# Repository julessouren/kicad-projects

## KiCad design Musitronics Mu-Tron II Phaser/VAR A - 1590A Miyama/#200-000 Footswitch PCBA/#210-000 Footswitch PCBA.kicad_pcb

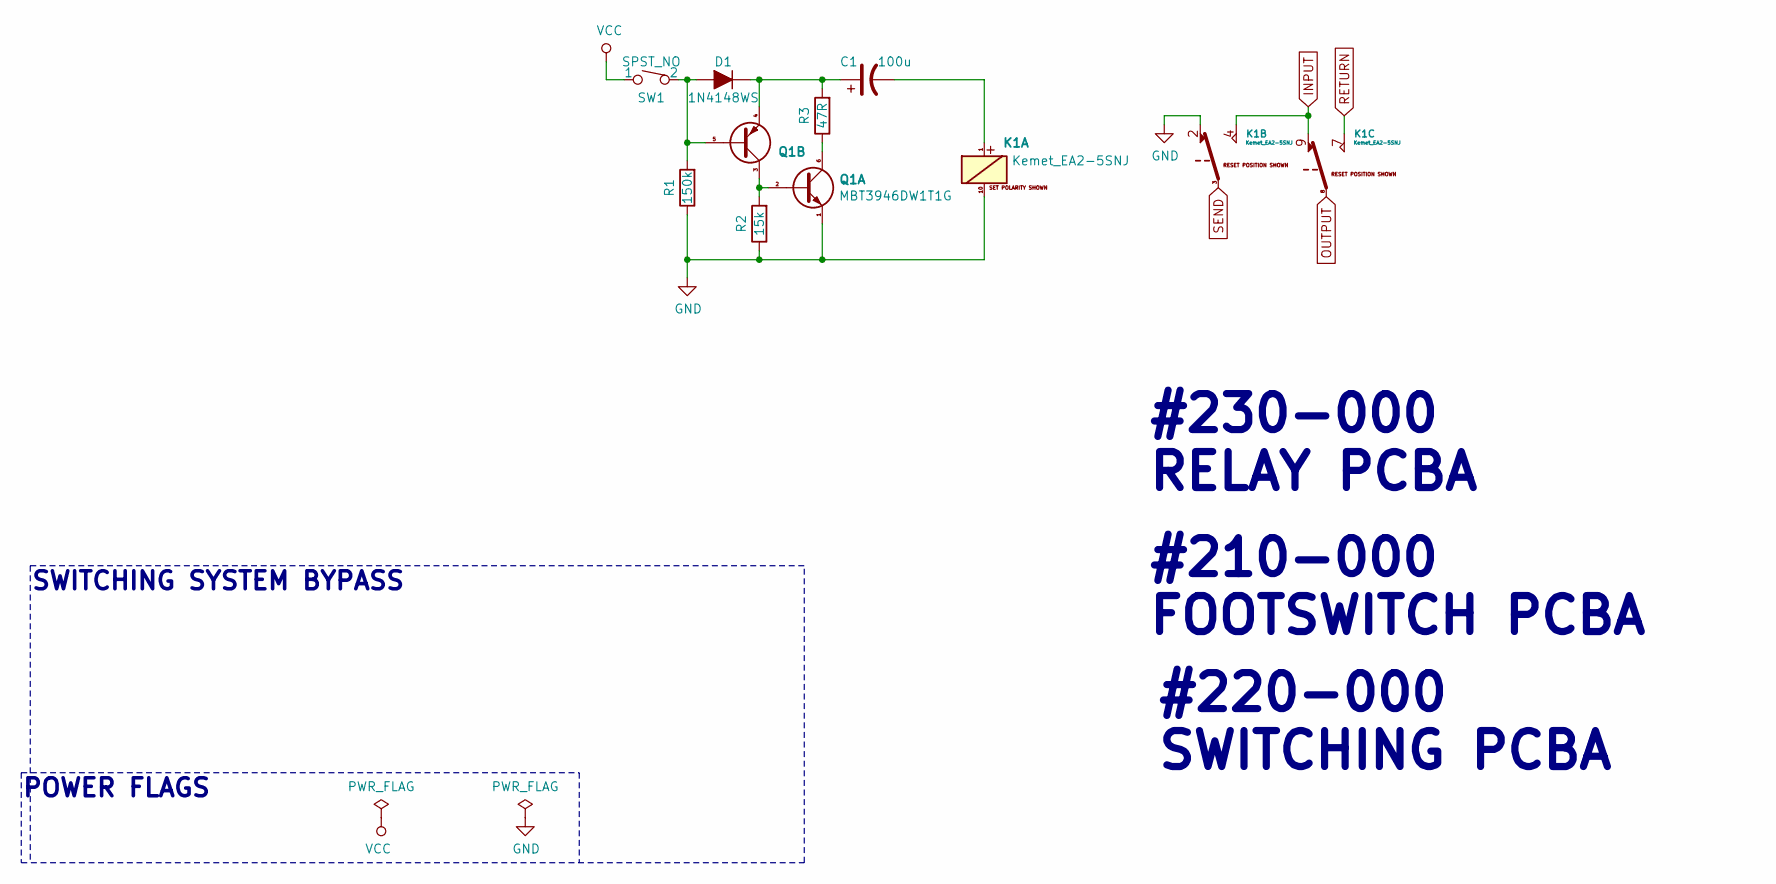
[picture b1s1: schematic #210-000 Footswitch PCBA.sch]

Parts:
C1: 100u; Nichicon_UWT1E101MCL1GS
D1: 1N4148WS; ON_Semi_1N4148WS
K1: Kemet_EA2-5SNJ; Kemet_EA2-SNJ
Q1: MBT3946DW1T1G; ON_Semi_MBT3946DW1T1G
R1: 150k; R_0603_1608M
R2: 15k; R_0603_1608M
R3: 47R; R_0603_1608M
SW1: SPST_NO; Miyama_DS-462

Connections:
GND: K1.2, K1.10, Q1.1 (E1), R1.1, R2.1
INPUT: K1.4, K1.9
unnamed: C1.1, D1.2 (K), Q1.4 (E2), R3.2
unnamed: C1.2, K1.1
unnamed: D1.1 (A), Q1.5 (B2), R1.2, SW1.2
unnamed: Q1.2 (B1), Q1.3 (C2), R2.2
unnamed: Q1.6 (C1), R3.1
OUTPUT: K1.8
RETURN: K1.7
SEND: K1.3
VCC: SW1.1

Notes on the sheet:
#210-000 FOOTSWITCH PCBA
#220-000 SWITCHING PCBA
SWITCHING SYSTEM BYPASS
POWER FLAGS
#230-000 RELAY PCBA

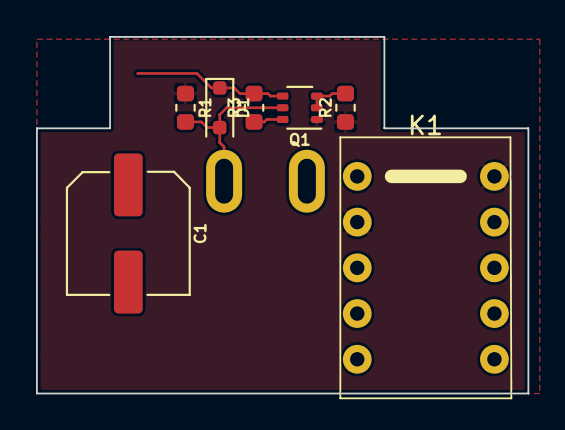
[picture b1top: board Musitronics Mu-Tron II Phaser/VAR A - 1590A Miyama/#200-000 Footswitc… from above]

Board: 2 copper layers, 27.3 x 19.8 mm, 8 parts (1 on the bottom side), 7 nets.

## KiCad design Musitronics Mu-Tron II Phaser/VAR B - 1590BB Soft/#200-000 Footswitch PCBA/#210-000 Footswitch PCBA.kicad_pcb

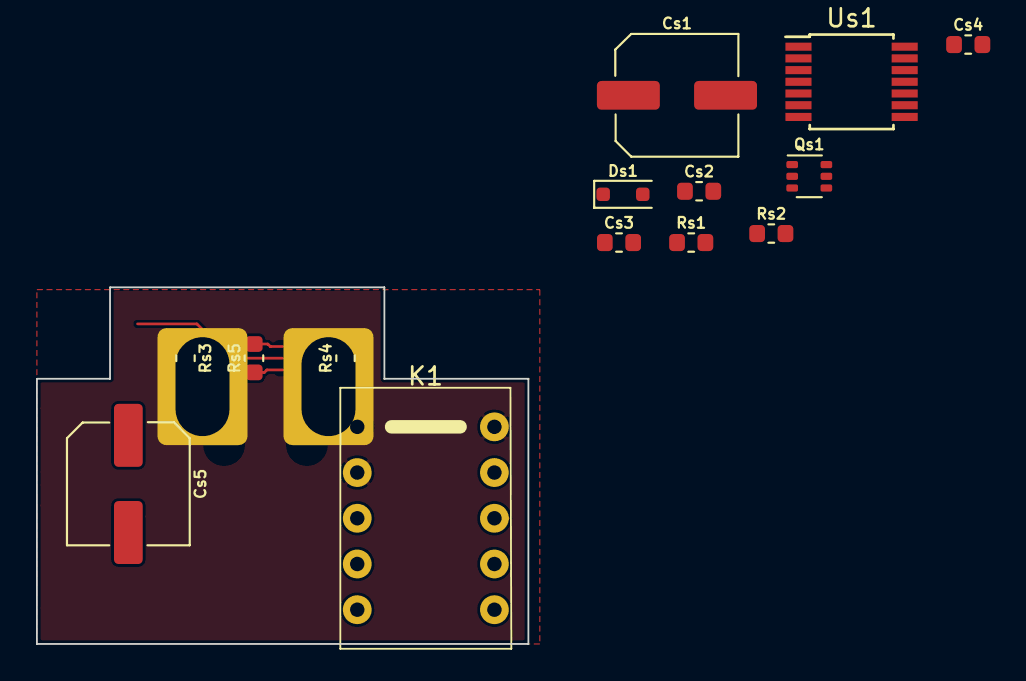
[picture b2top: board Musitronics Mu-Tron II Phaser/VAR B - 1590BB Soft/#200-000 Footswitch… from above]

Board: 2 copper layers, 27.3 x 19.8 mm, 15 parts (1 on the bottom side), 12 nets.

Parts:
Cs1, Cs5: 100u; Nichicon_UWT1E101MCL1GS
Cs2: 100n; C_0603_1608M_h0.85
Cs3: 4n7; C_0603_1608M_h0.85
Cs4: 47n; C_0603_1608M_h0.85
Ds1: 1N4148WS; ON_Semi_1N4148WS
K1: Kemet_EA2-5SNJ; Kemet_EA2-SNJ
Qs1: MBT3946DW1T1G; ON_Semi_MBT3946DW1T1G
Rs1: 100k; R_0603_1608M
Rs2: 1M; R_0603_1608M
Rs3: 150k; R_0603_1608M
Rs4: 15k; R_0603_1608M
Rs5: 47R; R_0603_1608M
SWa1: SPST_NO; R13-85A1-05-HWH
Us1: CD40106BPWR; Texas_Instruments_CD40106BPWR

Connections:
GND: Cs1.2, Cs2.2, Cs3.2, Cs4.2, K1.2, K1.10, Qs1.1, Rs3.1, Rs4.1, Us1.7, Us1.9, Us1.11, Us1.13
INPUT: K1.4, K1.9
unnamed: Cs3.1, Rs1.2, SWa1.1, Us1.1
unnamed: Cs4.1, Rs2.1, SWa1.2
unnamed: Cs5.1, Ds1.2, Qs1.4, Rs5.2
unnamed: Cs5.2, K1.1
unnamed: Ds1.1, Qs1.5, Rs3.2, Us1.6
unnamed: Qs1.2, Qs1.3, Rs4.2
unnamed: Qs1.6, Rs5.1
unnamed: Rs1.1, Us1.4, Us1.5
unnamed: Rs2.2, Us1.2, Us1.3
VCC: Cs1.1, Cs2.1, Us1.14

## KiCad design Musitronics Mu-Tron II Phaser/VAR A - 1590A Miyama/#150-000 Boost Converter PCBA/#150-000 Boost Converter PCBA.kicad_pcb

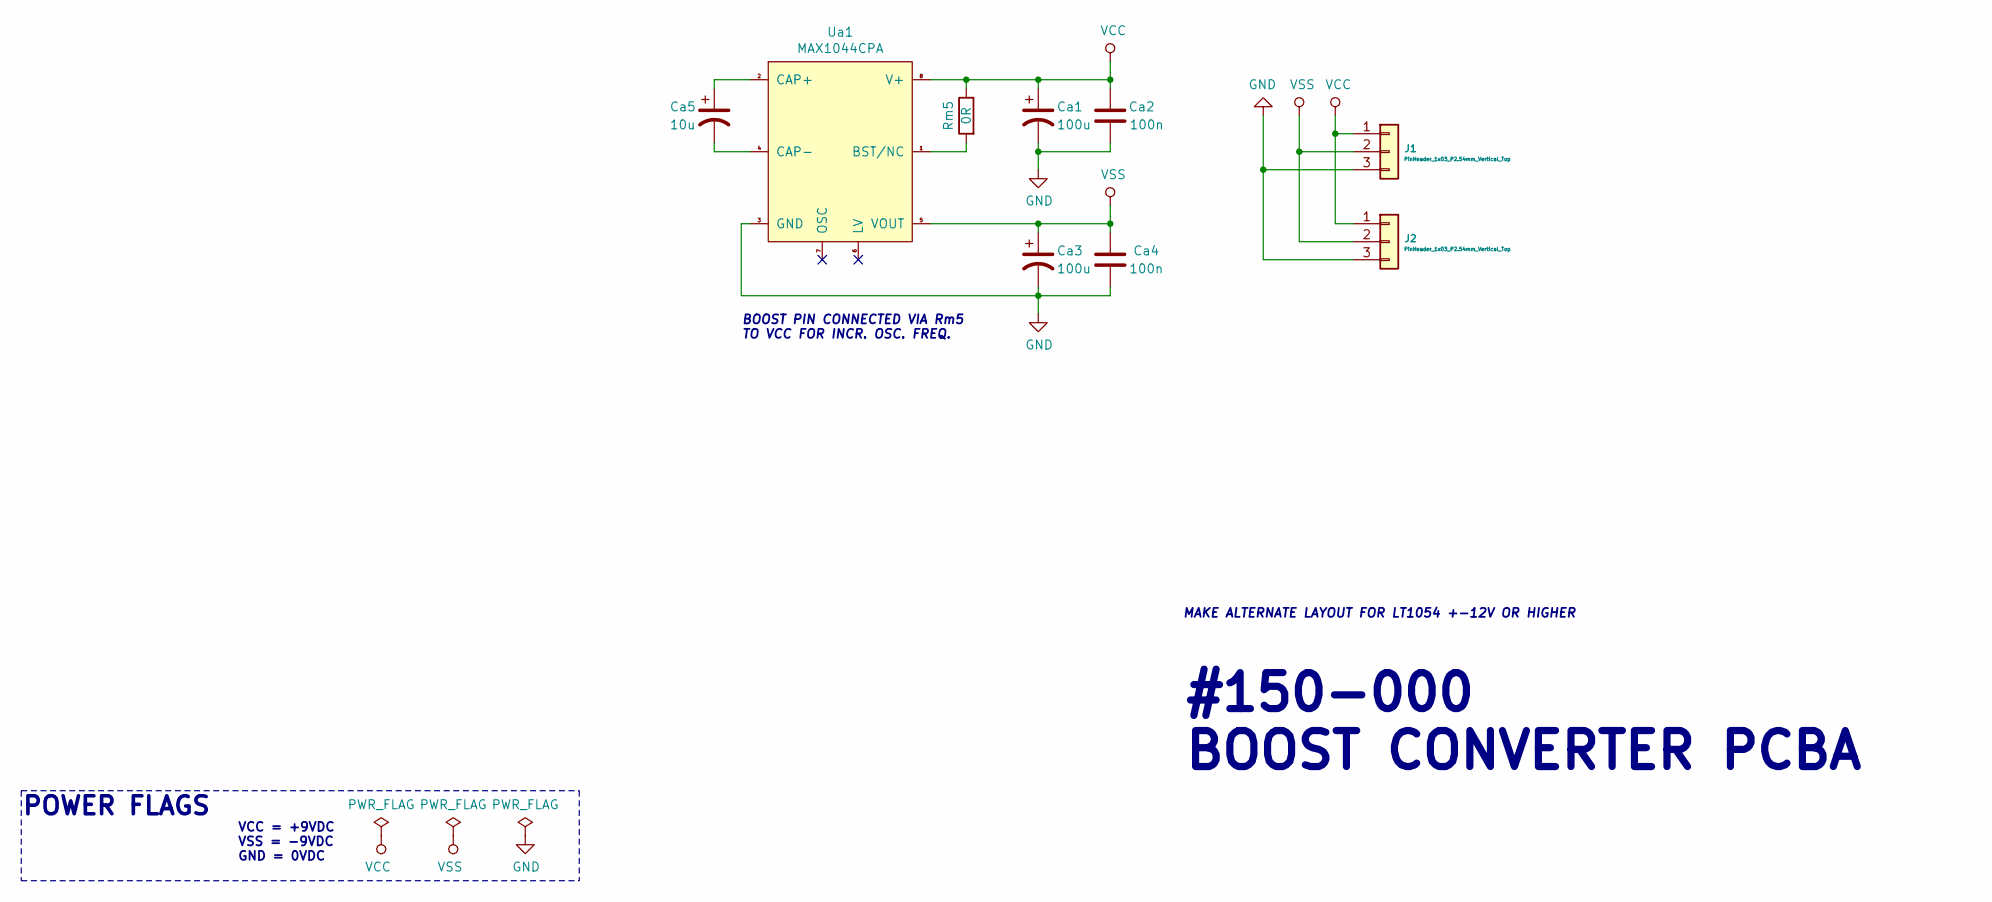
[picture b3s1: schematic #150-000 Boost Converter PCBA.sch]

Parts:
Ca1, Ca3: 100u; Nichicon_UWT1E101MCL1GS
Ca2, Ca4: 100n; C_0603_1608M_h0.85
Ca5: 10u; Nichicon_UWT1V100MCL1GB
J1, J2: PinHeader_1x03_P2.54mm_Vertical_Top
Rm5: 0R; R_0603_1608M
Ua1: MAX1044CPA

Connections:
GND: Ca1.2, Ca2.2, Ca3.2, Ca4.2, J1.3, J2.3, Ua1.3 (GND)
unnamed: Ca5.1, Ua1.2 (CAP+)
unnamed: Ca5.2, Ua1.4 (CAP-)
unnamed: Rm5.2, Ua1.1 (BST/NC)
VCC: Ca1.1, Ca2.1, J1.1, J2.1, Rm5.1, Ua1.8 (V+)
VSS: Ca3.1, Ca4.1, J1.2, J2.2, Ua1.5 (VOUT)

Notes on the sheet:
VCC = +9VDC VSS = -9VDC GND = 0VDC
BOOST PIN CONNECTED VIA Rm5 TO VCC FOR INCR. OSC. FREQ.
POWER FLAGS
#150-000 BOOST CONVERTER PCBA
MAKE ALTERNATE LAYOUT FOR LT1054 +-12V OR HIGHER

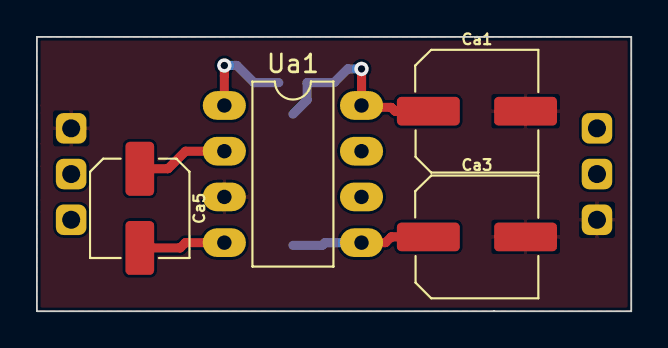
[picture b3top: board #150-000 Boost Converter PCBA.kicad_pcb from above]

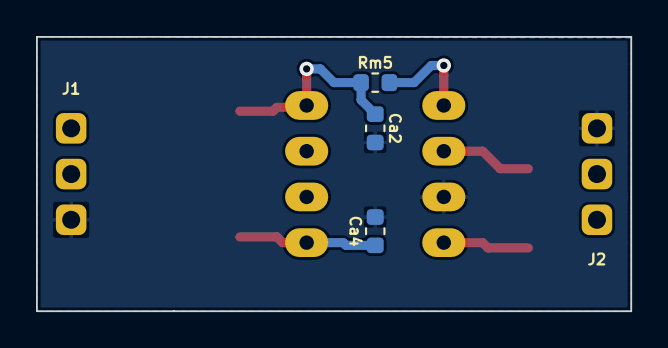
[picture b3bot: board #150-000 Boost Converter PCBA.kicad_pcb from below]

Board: 2 copper layers, 33.0 x 15.2 mm, 9 parts (5 on the bottom side), 6 nets.

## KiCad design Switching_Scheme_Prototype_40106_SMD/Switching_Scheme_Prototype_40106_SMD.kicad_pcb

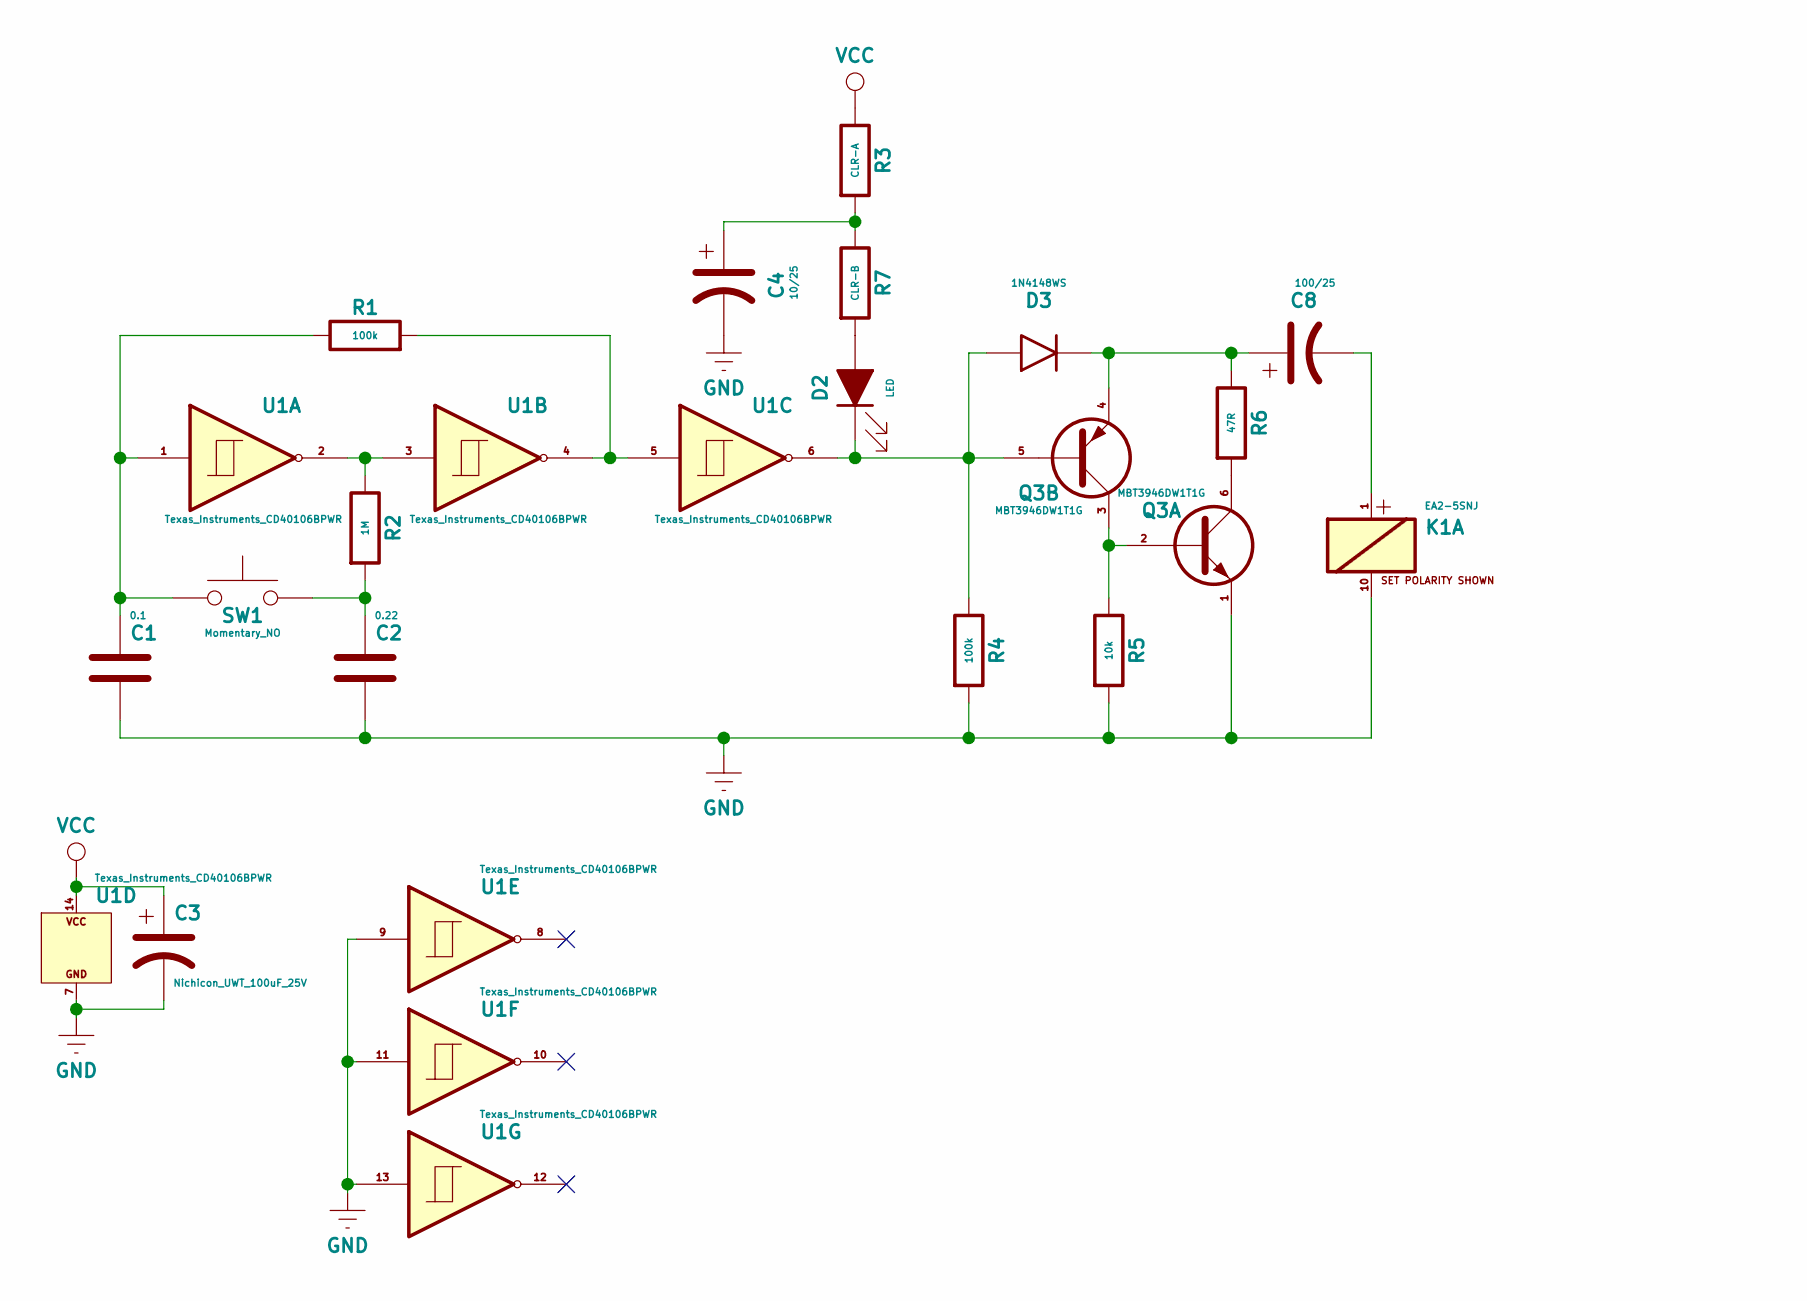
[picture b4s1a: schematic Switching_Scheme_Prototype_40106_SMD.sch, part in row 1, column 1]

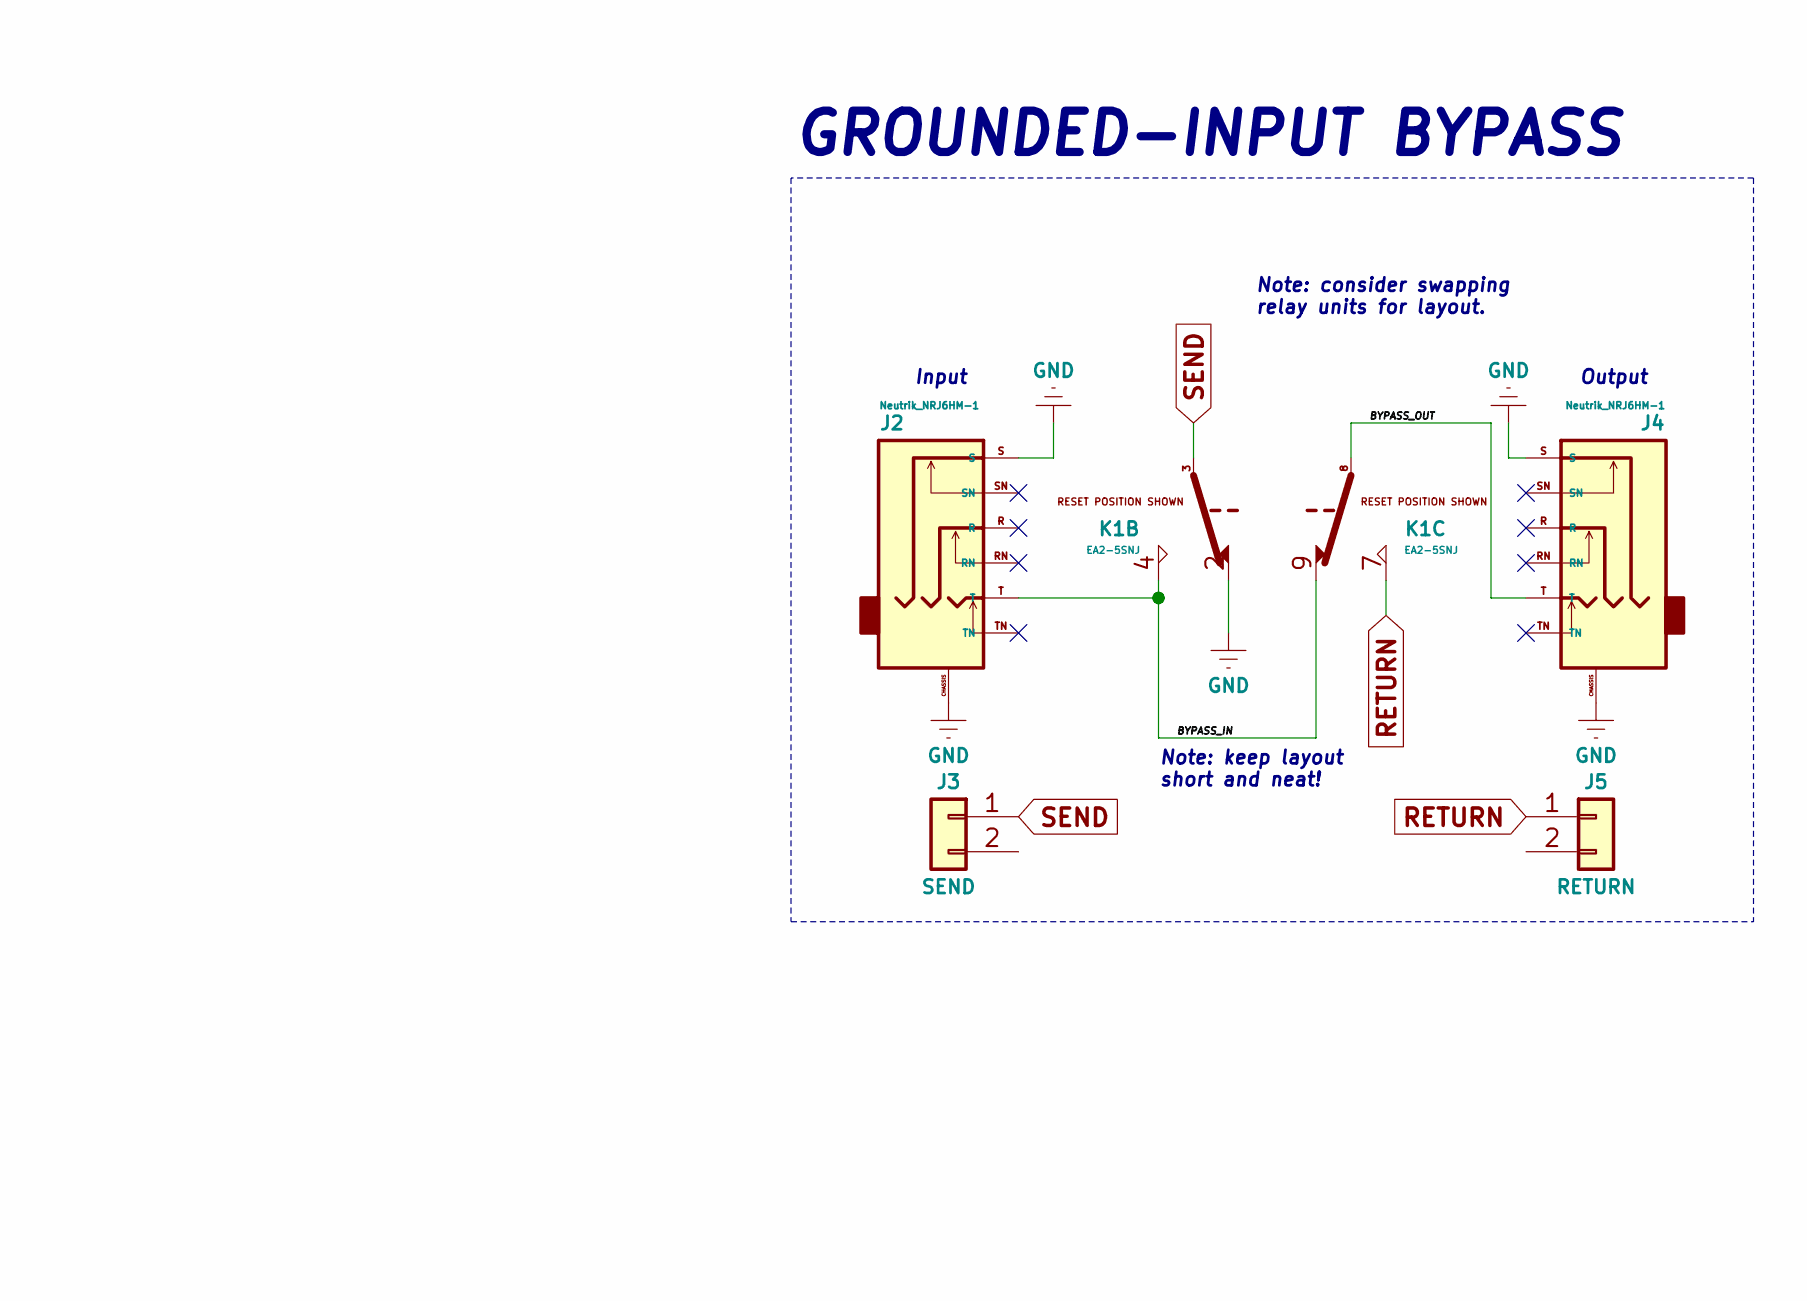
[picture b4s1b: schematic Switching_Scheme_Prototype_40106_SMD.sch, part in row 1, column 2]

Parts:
C1: 0.1; C_0603_1608M
C2: 0.22; C_0603_1608M
C3: Nichicon_UWT_100uF_25V; CP_EIA-7343-31_Kemet-D
C4: 10/25; CP_EIA-6032-28_Kemet-C
C8: 100/25; CP_EIA-7343-31_Kemet-D
D2: LED; PinHeader_1x02_P2.54mm_Vertical_Top
D3: 1N4148WS; ON_Semi_1N4148WS_SOD-323F-2
J2, J4: Neutrik_NRJ6HM-1
J3: SEND; PinHeader_1x02_P2.54mm_Vertical_Top
J5: RETURN; PinHeader_1x02_P2.54mm_Vertical_Top
K1: EA2-5SNJ; Kemet_EA2-5SNJ
Q3: MBT3946DW1T1G; ON_Semi_MBT3946DW1T1G_SOT-363_SC-70-6_SC-80
R1, R4: 100k; C_0603_1608M
R2: 1M; C_0603_1608M
R3: CLR-A; C_0603_1608M
R5: 10k; C_0603_1608M
R6: 47R; C_0603_1608M
R7: CLR-B; C_0603_1608M
SW1: Momentary_NO; PinHeader_1x02_P2.54mm_Vertical_Top
U1: Texas_Instruments_CD40106BPWR; Texas_Instruments_CD40106BPWR_TSSOP-14

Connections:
/BYPASS_IN: J2.T, K1.4, K1.9
/BYPASS_OUT: J4.T, K1.8
GND: C1.2, C2.2, C3.2, C4.2, J2.CHASSIS, J2.S, J4.CHASSIS, J4.S, K1.2, K1.10, Q3.1 (E1), R4.2, R5.2, U1.7, U1.9, U1.11, U1.13
unnamed: C1.1, R1.1, SW1.1, U1.1
unnamed: C2.1, R2.2, SW1.2
unnamed: C4.1, R3.2, R7.1
unnamed: C8.1, D3.1 (K), Q3.4 (E2), R6.1
unnamed: C8.2, K1.1
unnamed: D2.1 (K), D3.2 (A), Q3.5 (B2), R4.1, U1.6
unnamed: D2.2 (A), R7.2
unnamed: Q3.2 (B1), Q3.3 (C2), R5.1
unnamed: Q3.6 (C1), R6.2
unnamed: R1.2, U1.4, U1.5
unnamed: R2.1, U1.2, U1.3
RETURN: J5.1, K1.7
SEND: J3.1, K1.3
VCC: C3.1, R3.1, U1.14

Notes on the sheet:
GROUNDED-INPUT BYPASS
Input
Output
Note: keep layout short and neat!
Note: consider swapping relay units for layout.

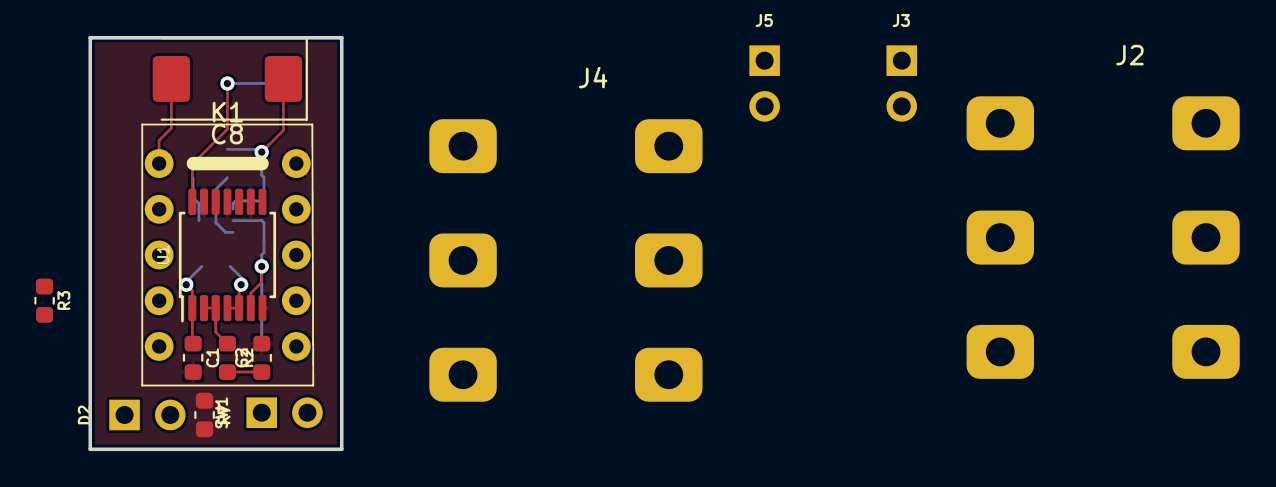
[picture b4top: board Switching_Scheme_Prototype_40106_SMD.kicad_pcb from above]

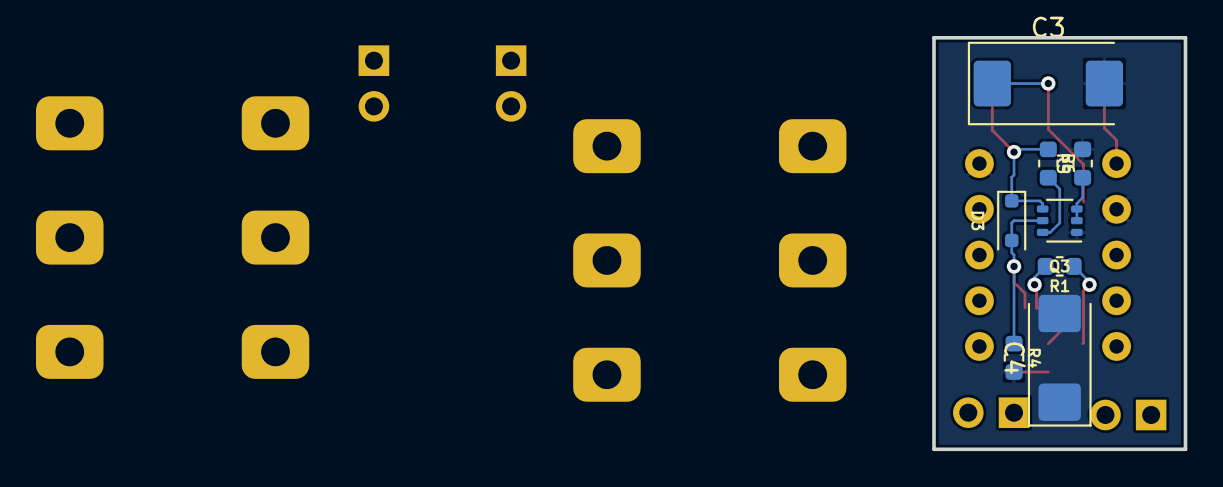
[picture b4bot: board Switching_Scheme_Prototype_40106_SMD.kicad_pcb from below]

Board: 2 copper layers, 14.0 x 22.9 mm, 22 parts (8 on the bottom side), 17 nets.

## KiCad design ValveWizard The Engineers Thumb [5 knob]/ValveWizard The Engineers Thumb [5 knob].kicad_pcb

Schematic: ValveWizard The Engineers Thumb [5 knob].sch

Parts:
C1: 47u; Nichicon_UWT1V470MCL1GS_47uF_35V_6.3x5.8mm
C2: 100n; C_0603_1608M
C3: 10n; C_0603_1608M
C4, C6: 100p; C_0603_1608M
C5, C7: 1u; Nichicon_UWT1H010MCL1GB_1.0uF_50V_4.0x5.4mm
C8: 10u; Nichicon_UWT1V100MCL1GB_10uF_35V_5.0x5.4mm
D1, D4, D5, D6: D_ALT; ON_Semi_1N4148WS_SOD-323F-2
D2, D3: LED_ALT; LED_0805_2012Metric
Q1: ON_Semi_2N3906TAR; ON_Semi_2N3906TAR_TO-92-3-P2.54
R1, R2, R11: 1M; R_0603_1608M
R3: 10M; R_0603_1608M
R4, R5, R8, R10, R14: 1k; R_0603_1608M
R6: 220k; R_0603_1608M
R7, R9, R13: 10k; R_0603_1608M
R12: 220R; R_0603_1608M
RV1, RV2, RV3, RV4: 1M; Alpha_Taiwan_RV16AF-10_THT
RV5: 10k; Alpha_Taiwan_RV16AF-10_THT
SW1: SW_BRIGHT; Wire_Pad_2x_1.2mm_Hole_2.0_Annular_2.54mm_Pitch
U1, U2: TL072; SOIC-8_3.9x4.9mm_P1.27mm
U3: LM13700; SOIC-16_3.9x9.9mm_P1.27mm

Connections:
+9.0VDC: C1.1, D1.1 (K), R1.1
GND: C1.2, C2.2, C5.2, C7.2, D1.2 (A), D2.2 (A), D3.1 (K), R2.2, R3.2, RV5.1
unnamed: C2.1, R1.2, R2.1, U1.5
unnamed: C3.1, D2.1 (K), D3.2 (A), R4.1
unnamed: C3.2, RV1.3, U1.3
unnamed: C4.1, R5.2, RV2.1, U1.2
unnamed: C4.2, C8.1, R13.1, RV2.2, U1.1
unnamed: C5.1, R6.2, R8.2, RV4.1
unnamed: C6.1, R7.2
unnamed: C6.2, SW1.1 (A)
unnamed: C7.1, R8.1, U2.3
unnamed: C8.2, R14.2
unnamed: D4.1 (K), RV3.2, RV3.3, U2.6
unnamed: D4.2 (A), D5.1 (K), U2.7
unnamed: D5.2 (A), RV4.2, RV4.3
unnamed: D6.1 (K), Q1.2, R10.2, U2.2
unnamed: D6.2 (A), Q1.1, U2.1
unnamed: Q1.3, R11.2, U3.1
unnamed: R3.1, R4.2
unnamed: R5.1, R7.1, R9.1
unnamed: R6.1, RV3.1
unnamed: R12.2, R13.2, U3.3 (+)
unnamed: R14.1, RV5.3
unnamed: RV1.2, U2.5
VREF: R9.2, R10.1, R11.1, R12.1, RV1.1, SW1.2 (B), U1.6, U1.7, U3.4 (-), U3.5

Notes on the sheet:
THRESHOLD
ATTACK
RELEASE
BRIGHT
RATIO
LEVEL
Schematic source: http://www.freestompboxes.org/download/file.php?id=31228&t=1
Add no connects to unused OTA half

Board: 2 copper layers, 38 parts (0 on the bottom side), 25 nets, no tracks yet.

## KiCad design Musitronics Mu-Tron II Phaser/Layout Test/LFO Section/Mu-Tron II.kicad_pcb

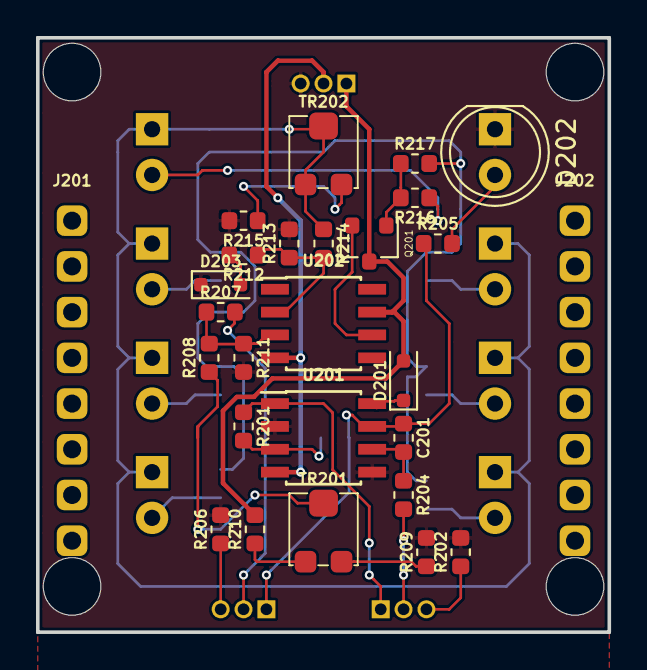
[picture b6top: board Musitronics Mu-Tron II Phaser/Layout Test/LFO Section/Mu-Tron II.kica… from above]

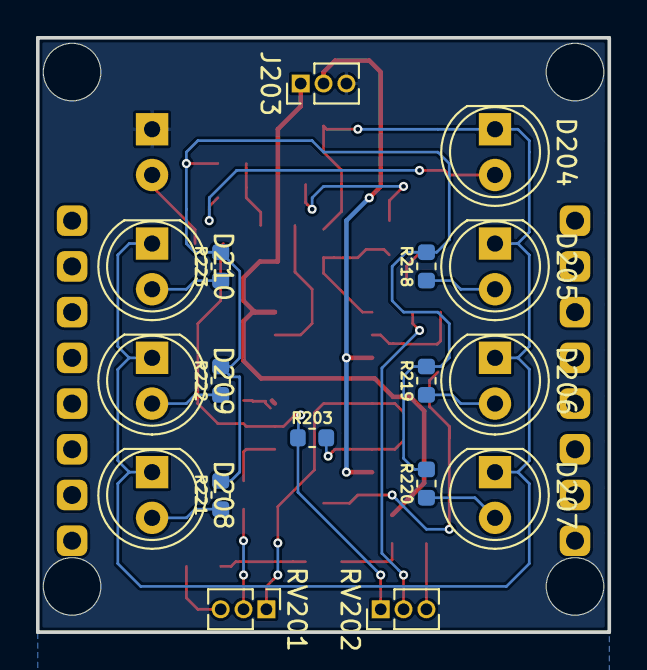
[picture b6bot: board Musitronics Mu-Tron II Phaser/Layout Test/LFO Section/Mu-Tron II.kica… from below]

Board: 2 copper layers, 31.8 x 33.0 mm, 44 parts (17 on the bottom side), 31 nets.

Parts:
C201: 470n; C_0603_1608M
D201, D203: 1N4148; ON_Semi_1N4148WS_SOD-323F-2
D202: LED_RATE; LED_D5.0mm_Yellow
D204: LED_LFO_0; LED_D5.0mm_Yellow
D205: LED_LFO_1; LED_D5.0mm_Yellow
D206: LED_LFO_2; LED_D5.0mm_Yellow
D207: LED_LFO_3; LED_D5.0mm_Yellow
D208: LED_LFO_4; LED_D5.0mm_Yellow
D209: LED_LFO_5; LED_D5.0mm_Yellow
D210: LED_LFO_6; LED_D5.0mm_Yellow
J201, J202: Conn_01x08; PinHeader_1x08_P2.54mm_Vertical_Bottom
J203: Conn_01x03; PinHeader_1x03_P1.27mm_Vertical
Q201: 2N4401; ON_Semi_SMMBT4401LT1G_SOT-23
R201, R207, R213: 68k; R_0603_1608M
R202: 120R; R_0603_1608M
R203, R208: 47k; R_0603_1608M
R204: 39k; R_0603_1608M
R205: CLR_RATE; R_0603_1608M
R206: 560R; R_0603_1608M
R209, R210: 2k2; R_0603_1608M
R211: 3k6; R_0603_1608M
R212: 10k; R_0603_1608M
R214: 220k; R_0603_1608M
R215: 390R; R_0603_1608M
R216, R217, R218, R219, R220, R221, R222, R223: 0R; R_0603_1608M
RV201: A25k; PinHeader_1x03_P1.27mm_Vertical
RV202: B10k; PinHeader_1x03_P1.27mm_Vertical
TR201: 10k; Bourns_TC33X-2-104E
TR202: 1k; Bourns_TC33X-2-104E
U201: TL062; SOIC-8_3.9x4.9mm_P1.27mm
U202: TL071; SOIC-8_3.9x4.9mm_P1.27mm

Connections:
/LFO Section/VDD_LFO: D201.1, U201.8
GND: D202.1, D203.1, J203.3, R202.2, R206.2, R209.2, R211.2, R213.2, R215.2, U201.2, U201.5
unnamed: C201.1, R203.1, R205.1, RV202.1, U201.7
unnamed: C201.2, R204.1, U201.6
unnamed: D202.2, R205.2
unnamed: D203.2, R212.2
unnamed: D204.1, D205.1, D206.1, D207.1, D208.1, D209.1, D210.1, R214.1, TR202.1, TR202.2
unnamed: D204.2, R216.1
unnamed: D205.2, R218.1
unnamed: D206.2, R219.1
unnamed: D207.2, R220.1
unnamed: D208.2, R221.1
unnamed: D209.2, R222.1
unnamed: D210.2, R223.1
unnamed: Q201.1, R216.2, R217.1
unnamed: Q201.2, U202.6
unnamed: R201.1, RV201.1, U201.1
unnamed: R201.2, R203.2, U201.3
unnamed: R202.1, RV201.3
unnamed: R204.2, RV201.2
unnamed: R206.1, RV202.3
unnamed: R207.1, R208.2, R211.1, U202.3
unnamed: R207.2, RV202.2
unnamed: R208.1, TR201.2
unnamed: R209.1, TR201.3
unnamed: R210.1, TR201.1
unnamed: R212.1, R213.1, R214.2, U202.2
unnamed: R215.1, TR202.3
unnamed: R217.2, R218.2, R219.2, R220.2, R221.2, R222.2, R223.2
VDD: D201.2, J203.1, Q201.3, R210.2, U202.7
VEE: J203.2, U201.4, U202.4

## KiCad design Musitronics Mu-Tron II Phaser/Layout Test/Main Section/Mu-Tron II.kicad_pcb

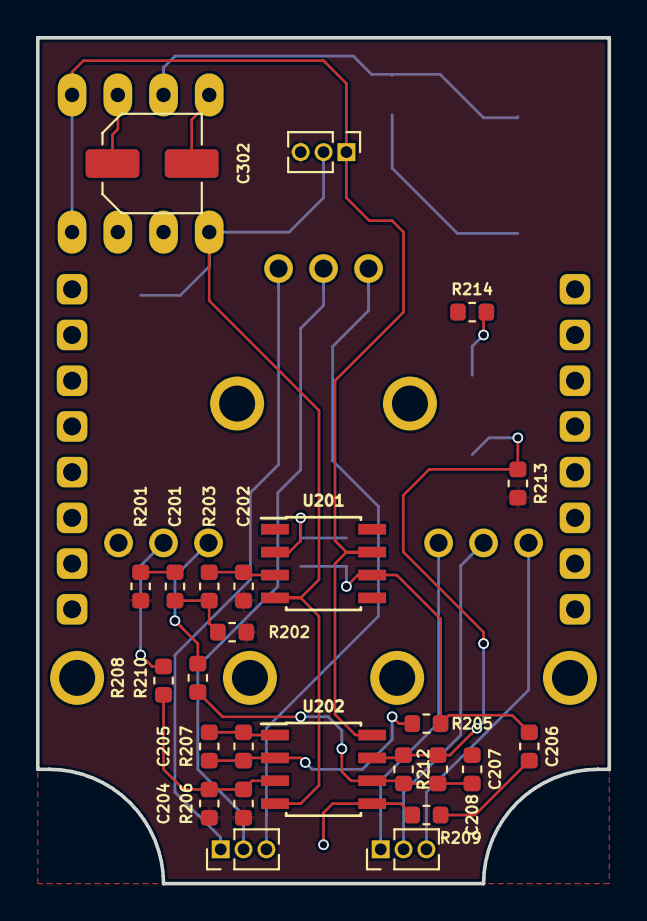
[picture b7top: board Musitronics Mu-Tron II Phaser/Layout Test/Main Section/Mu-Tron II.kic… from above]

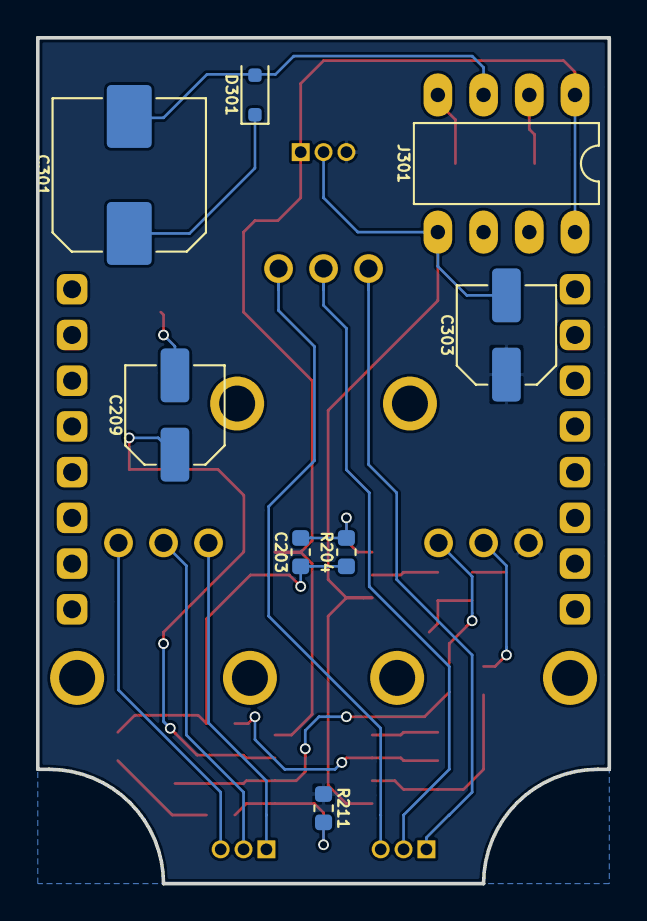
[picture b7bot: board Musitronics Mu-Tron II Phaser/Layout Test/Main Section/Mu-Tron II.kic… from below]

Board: 2 copper layers, 31.8 x 47.0 mm, 38 parts (11 on the bottom side), 28 nets.

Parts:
C201, C203: 100n; C_0603_1608M
C202: 47p; C_0603_1608M
C204: 3n3; C_0603_1608M
C205: 1n; C_0603_1608M
C206: 1u; C_0603_1608M
C207: 470n; C_0603_1608M
C208: 820p; C_0603_1608M
C209, C302, C303: 10u; Nichicon_UWT1V100MCL1GB_10uF_35V_5.0x5.4mm
C301: 220u; Nichicon_UWT1E221MNL1GS_220uF_25V_8.0x10.0mm
D301: 1N4001; ON_Semi_1N4148WS_SOD-323F-2
J201, J202: Conn_01x08; PinHeader_1x08_P2.54mm_Vertical_Top
J203, J204, J208: Conn_01x03; PinHeader_1x03_P1.27mm_Vertical
J301: 1044; DIP-8_W7.62mm_Socketed
R201: RPD_IN; R_0603_1608M
R202, R204: 390k; R_0603_1608M
R203: 3k9; R_0603_1608M
R205, R206, R207: 4k7; R_0603_1608M
R208, R211, R212: 8k2; R_0603_1608M
R209, R210: 10k; R_0603_1608M
R213: 18k; R_0603_1608M
R214: 560R; R_0603_1608M
RV201: A10k; Alpha_Taiwan_RD901F-40
RV202: A25k; Alpha_Taiwan_RD901F-40
RV203: B10k; Alpha_Taiwan_RD901F-40
U201: TL071; SOIC-8_3.9x4.9mm_P1.27mm
U202: TL072; SOIC-8_3.9x4.9mm_P1.27mm

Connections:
/Main Section/FX_IN: C201.2, R201.1
/Main Section/LDR_IN: C205.1, R207.1, U202.1
GND: C202.2, C204.2, C303.1, J208.3, R201.2, R202.2, R206.1, R211.1, R213.2, RV201.1
unnamed: C201.1, R202.1, R203.2
unnamed: C202.1, R203.1, U201.3
unnamed: C203.1, C206.2, R204.1, R205.2, U201.6
unnamed: C203.2, R204.2, U201.2
unnamed: C204.1, R206.2, R208.1, U202.3
unnamed: C205.2, R205.1, R207.2, U202.2
unnamed: C206.1, R209.2
unnamed: C207.1, C208.2, R210.1, R212.2, U202.6
unnamed: C208.1, C209.1, R212.1, R213.1, U202.7
unnamed: C209.2, R214.2
unnamed: C301.2, D301.2, J301.3
unnamed: C302.1, J301.2
unnamed: C302.2, J301.4
unnamed: J203.1, RV202.1
unnamed: J203.2, RV202.2
unnamed: J203.3, RV202.3
unnamed: J204.1, RV203.1
unnamed: J204.2, RV203.2
unnamed: J204.3, RV203.3
unnamed: R208.2, RV201.2
unnamed: R209.1, R211.2, U202.5
unnamed: R210.2, RV201.3
VCC: C301.1, D301.1
VDD: J208.1, J301.1, J301.8, U201.7, U202.8
VEE: C303.2, J208.2, J301.5, U201.4, U202.4

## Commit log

2018-11-25 Start schematic and layout
2018-11-25 Update fp-info-cache
2018-12-05 us8 based switching files
2018-12-06 Added designer notes for bistable
2018-12-09 Breakout SM8 DCT
2018-12-16 dct us8 breakout
2018-12-29 cache changes
2019-01-04 Changed directory
2019-02-05 Breakout and utility boards
2019-02-05 Created revision A for breakout and utility boards
    Created revision A for breakout and utility boards
    - ON Semi MBT3946DW1T1G
    - ON Semi MCH6341-TL-W
    - ON Semi NCP1117LPST50T3G
    - ON Semi NL37WZ14USG
    - Texas Instruments SN74LVC3G14DCTR
2019-02-05 Revision A boards checked before sending off to fab
2019-02-05 Added 0402 breakout board
2019-02-05 Added 0402 / 0603 passives breakout
2019-02-07 Added sandwich relay switching pcba's
2019-02-08 Cleanup
2019-02-27 Various projects
2019-02-28 Added Engineers Thumb
2019-02-28 detox
2019-03-25 mu-tron ii major work
2019-04-12 mu-tron update, bom
2019-04-13 Projects upd
2019-04-14 JFET Matching Schemes started
2019-04-16 updated jfet matching scheme, eng. thumb. symbol rescue
2019-04-19 40106 switching new
2019-07-16 MuTron Factory Schematic
2019-07-16 switching
2019-07-18 edit computer 2
2019-07-18 Revert "edit computer 2"
    This reverts commit 52804b7d86e33d0668af1082d22f36fcd7cbbfe3.
2019-07-18 Revert "Merge branch 'master' of https://github.com/julessouren/kicad-projects"
    This reverts commit d2ea240a84a9fc063b89791675447d3d816db0e3, reversing
    changes made to 39ac920bbc5a4d42ea6f5ab5cf061cab4b611eaa.
2019-07-18 Revert "Revert "Merge branch 'master' of https://github.com/julessouren/kicad-projects""
    This reverts commit 2f831e2ced40f723fe311d7100b534c1c0ef87c8.
2019-07-20 cache edit
2019-08-02 cache
